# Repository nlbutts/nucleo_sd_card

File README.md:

# nucleo_sd_card
SD Card PCB for ST Nucleo boards

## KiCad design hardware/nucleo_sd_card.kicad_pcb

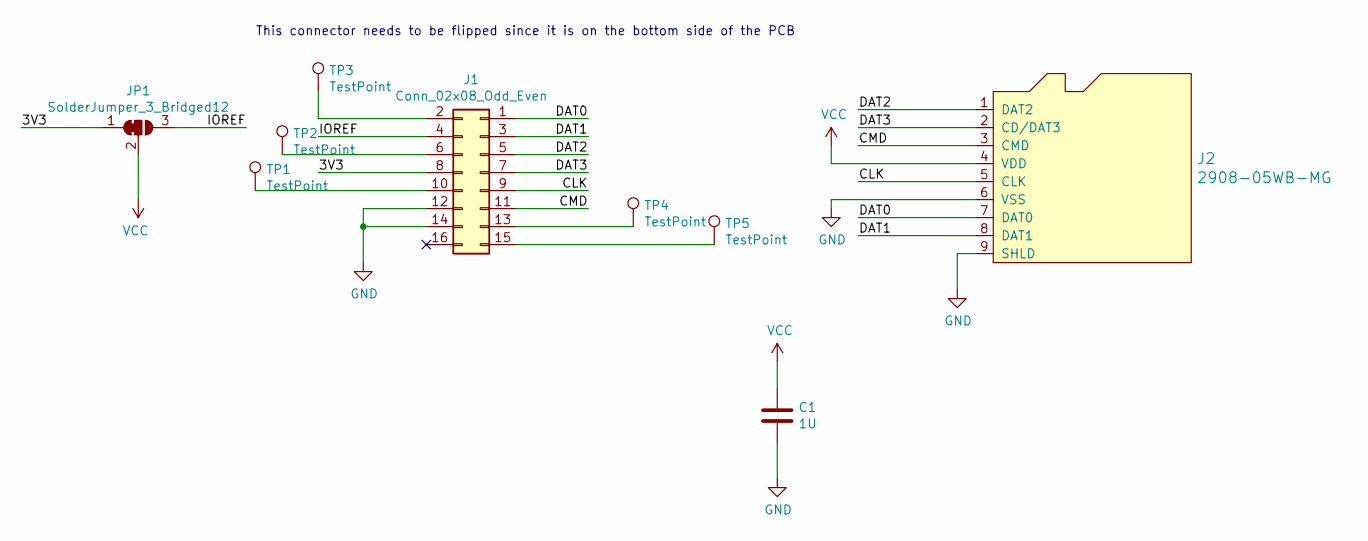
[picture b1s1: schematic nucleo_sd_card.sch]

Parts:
C1: 1U; C_0805_2012Metric_Pad1.15x1.40mm_HandSolder
J1: Conn_02x08_Odd_Even; PinHeader_2x08_P2.54mm_Vertical_SMD
J2: 2908-05WB-MG; AMPHENOL_1140084168; MPN 2908-05WB-MG; Digi-Key_PN 3M5607CT-ND
JP1: SolderJumper_3_Bridged12; SolderJumper-3_P1.3mm_Bridged12_RoundedPad1.0x1.5mm_NumberL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
TP1, TP2, TP3, TP4, TP5: TestPoint; TestPoint_Pad_D1.0mm

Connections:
/3V3: J1.8, JP1.1 (A)
/CLK: J1.9, J2.5 (CLK)
/CMD: J1.11, J2.3 (CMD)
/DAT0: J1.1, J2.7 (DAT0)
/DAT1: J1.3, J2.8 (DAT1)
/DAT2: J1.5, J2.1 (DAT2)
/DAT3: J1.7, J2.2 (CD/DAT3)
/IOREF: J1.4, JP1.3 (B)
GND: C1.2, J1.12, J1.14, J2.6 (VSS), J2.9 (SHLD)
unnamed: J1.2, TP3.1
unnamed: J1.6, TP2.1
unnamed: J1.10, TP1.1
unnamed: J1.13, TP4.1
unnamed: J1.15, TP5.1
VCC: C1.1, J2.4 (VDD), JP1.2 (C)

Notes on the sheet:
This connector needs to be flipped since it is on the bottom side of the PCB

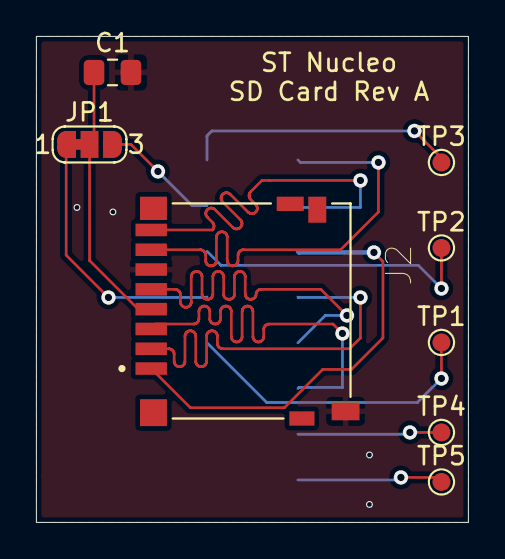
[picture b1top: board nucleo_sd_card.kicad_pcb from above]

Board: 2 copper layers, 24.0 x 27.0 mm, 9 parts (1 on the bottom side), 15 nets.

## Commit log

2020-11-24 Initial checkin.
